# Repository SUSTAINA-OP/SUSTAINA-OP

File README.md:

<h1 align="center">
  SUSTAINA-OP&trade;
</h1>
  <p align="center">
    Open Hardware Platform Humanoid Robot
  </P>
  <p align="center">
    <image src="https://github.com/SUSTAINA-OP/.github/assets/53966390/7b5091e7-2190-424d-ae3a-13d850ef4622" width="640px" align="center"><br>
    SUSTAINA-OP&trade; RoboCup2022 Edition 
  </P>
      
## What is SUSTAINA-OP&trade; ?
SUSTAINA-OP&trade; is an open hardware platform developed to reduce the high cost of developing robot hardware. It is designed by Masato Kubotera, based on the "[Gankenkun](https://github.com/citbrains/OpenPlatform)" robot series developed by Hiroaki Shimoyoshi. SUSTAINA-OP&trade; was adopted as the official robot of the team "[CIT Brains](https://github.com/citbrains)" of Chiba Institute of Technology in Japan, and won the world championship of RoboCup Humanoid League KidSize in 2022.

> [!CAUTION]
> Copyright for SUSTAINA-OP&trade; is held by Masato Kubotera, not by CIT Brains. The copyright has not been completely abandoned.

## Development Environments
The mechanism for this product was designed in **Autodesk Inventor 2022**.

## License Information
This product is open source. Please review the [LICENSE](/LICENSE) for license information.<br>

This product by Masato Kubotera is licensed under a [CC BY-NC-SA 4.0 DEED](http://creativecommons.org/licenses/by-nc-sa/4.0/).

> [!NOTE]
> **Summary:**
> - **Attribution** — You must give appropriate credit , provide a link to the license, and indicate if changes were made.
> - **NonCommercial** — You may not use the material for commercial purposes.
> - **ShareAlike** — If you remix, transform, or build upon the material, you must distribute your contributions under the same license as the original.

> [!TIP]
> - **Examples of appropriate credit** — [SUSTAINA-OP&trade;](https://github.com/SUSTAINA-OP/SUSTAINA-OP) &copy; Masato Kubotera (2022) CC BY-NC-SA 4.0 DEED
> >
> - **Reference & Citation**  
>   To reference and/or cite the work contained in this repository, please use the following publications:
>   - Kubotera, M. and Hayashibara, Y.: SUSTAINA-OP&trade;: Kid-sized Open Hardware Platform Humanoid Robot with Emphasis on Sustainability. RoboCup 2023: Robot World Cup XXVI, pp.166–178 (2024) [Springer](https://link.springer.com/chapter/10.1007/978-3-031-55015-7_14)

> [!IMPORTANT]
> - **Handling of work products** — All work products related to SUSTAINA-OP&trade; should be released as open source, even if they are utilized in a narrow community where closed development may be a priority.
> - **Request for prior inquiry** —  The developer of SUSTAINA-OP&trade; is currently employed at the Chiba Institute of Technology. If you are a student at or related to the University and wish to use the SUSTAINA-OP&trade; deliverables, please contact us in advance.

## Acknowledgements
SUSTAINA-OP&trade; is a robot that incorporates the expertise accumulated by former CIT Brains members who participated in the RoboCup Humanoid League. CIT Brains members collaborated with us in building the actual robots. Additionally, I drew inspiration from various open-source hardware while designing and developing the robot. I would like to express my gratitude to these individuals.

## Contact
If you have any questions, please contact the designer of this product, Masato Kubodera, by [E-mail](masatokubotera06@yahoo.co.jp).

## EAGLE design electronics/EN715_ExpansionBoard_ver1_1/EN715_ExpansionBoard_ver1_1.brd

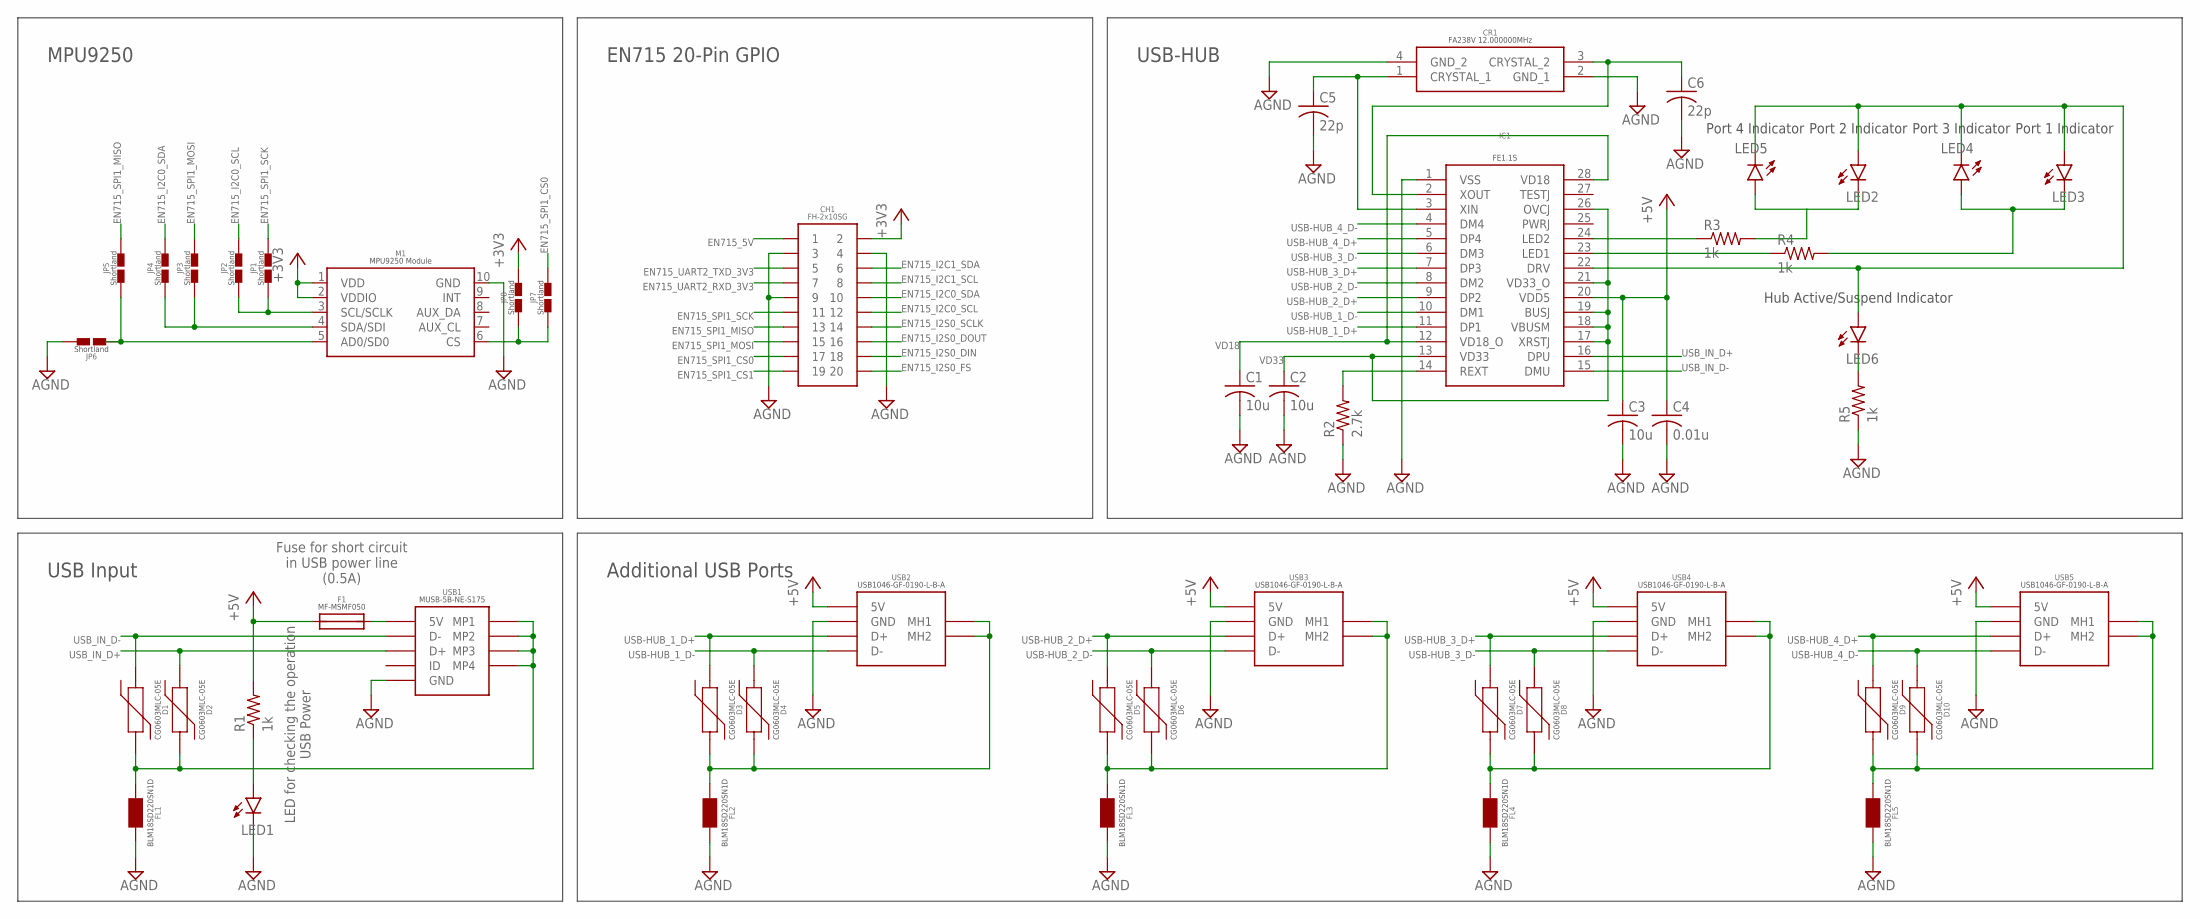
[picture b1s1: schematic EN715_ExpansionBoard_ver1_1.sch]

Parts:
C1, C2, C3: 10u; C0603
C4: 0.01u; C0603
C5, C6: 22p; C0603
CH1: 2X10
CR1: FA238V_12.000000MHZ; FA238V
D1, D2, D3, D4, D5, D6, D7, D8, D9, D10: CG0603MLC-05E
F1: MF-MSMF050
FL1, FL2, FL3, FL4, FL5: BLM18SD220SN1D
IC1: FE1.1S
JP1, JP2, JP3, JP4, JP5, JP6, JP7, JP8: SHORTLAND
LED1, LED2, LED3, LED4, LED5, LED6: LEDSML0603; SML0603
M1: MPU9250_MODULE
R1, R3, R4, R5: 1k; R0603
R2: 2.7k; R0603
USB1: MINI_USB_B_SMD
USB2, USB3, USB4, USB5: USB_A_X1_SMD

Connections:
+3V3: CH1.2, JP8.2, M1.1 (VDD), M1.2 (VDDIO)
+5V: C3.1, C4.1, F1.1, IC1.20 (VDD5), R1.2, USB2.1 (5V), USB3.1 (5V), USB4.1 (5V), USB5.1 (5V)
AGND: C1.2, C2.2, C3.2, C4.2, C5.2, C6.2, CH1.3, CH1.4, CH1.9, CR1.2 (GND_1), CR1.4 (GND_2), FL1.2, FL2.2, FL3.2, FL4.2, FL5.2, IC1.1 (VSS), JP6.2, LED1.C, M1.10 (GND), R2.1, R5.1, USB1.5 (GND), USB2.4 (GND), USB3.4 (GND), USB4.4 (GND), USB5.4 (GND)
B_FUSE_USB_MINI_B: F1.2, USB1.1 (5V)
EN715_5V: CH1.1
EN715_I2C0_SCL: CH1.12, JP2.2
EN715_I2C0_SDA: CH1.10, JP4.2
EN715_I2C1_SCL: CH1.8
EN715_I2C1_SDA: CH1.6
EN715_I2S0_DIN: CH1.18
EN715_I2S0_DOUT: CH1.16
EN715_I2S0_FS: CH1.20
EN715_I2S0_SCLK: CH1.14
EN715_SPI1_CS0: CH1.17, JP7.2
EN715_SPI1_CS1: CH1.19
EN715_SPI1_MISO: CH1.13, JP5.2
EN715_SPI1_MOSI: CH1.15, JP3.2
EN715_SPI1_SCK: CH1.11, JP1.2
EN715_UART2_RXD_3V3: CH1.7
EN715_UART2_TXD_3V3: CH1.5
FE1.1S_DRV: IC1.22 (DRV), LED2.A, LED3.A, LED4.C, LED5.C, LED6.A
FE1.1S_DRV_LED_A: LED6.C, R5.2
FE1.1S_LED1_A: LED3.C, LED4.A, R4.2
FE1.1S_LED_1_B: IC1.23 (LED1), R4.1
FE1.1S_LED_2_A: LED2.C, LED5.A, R3.2
FE1.1S_LED_2_B: IC1.24 (LED2), R3.1
LED_USBIN: LED1.A, R1.1
MPU9250_AD0/SD0: JP5.1, JP6.1, M1.5 (AD0/SD0)
MPU9250_CS: JP7.1, JP8.1, M1.6 (CS)
MPU9250_SCL/SCLK: JP1.1, JP2.1, M1.3 (SCL/SCLK)
MPU9250_SDA/SDI: JP3.1, JP4.1, M1.4 (SDA/SDI)
REXT_FE1.1S: IC1.14 (REXT), R2.2
USB-HUB_1_D+: D3.1, IC1.11 (DP1), USB2.3 (D+)
USB-HUB_1_D-: D4.1, IC1.10 (DM1), USB2.2 (D-)
USB-HUB_2_D+: D5.1, IC1.9 (DP2), USB3.3 (D+)
USB-HUB_2_D-: D6.1, IC1.8 (DM2), USB3.2 (D-)
USB-HUB_3_D+: D7.1, IC1.7 (DP3), USB4.3 (D+)
USB-HUB_3_D-: D8.1, IC1.6 (DM3), USB4.2 (D-)
USB-HUB_4_D+: D9.1, IC1.5 (DP4), USB5.3 (D+)
USB-HUB_4_D-: D10.1, IC1.4 (DM4), USB5.2 (D-)
USB_A_1_SHIELD: D3.2, D4.2, FL2.1, USB2.MH1, USB2.MH2
USB_A_2_SHIELD: D5.2, D6.2, FL3.1, USB3.MH1, USB3.MH2
USB_A_3_SHIELD: D7.2, D8.2, FL4.1, USB4.MH1, USB4.MH2
USB_A_4_SHIELD: D9.2, D10.2, FL5.1, USB5.MH1, USB5.MH2
USB_IN_D+: D2.1, IC1.16 (DPU), USB1.3 (D+)
USB_IN_D-: D1.1, IC1.15 (DMU), USB1.2 (D-)
USB_MINI_B_SHIELD: D1.2, D2.2, FL1.1, USB1.MP1, USB1.MP2, USB1.MP3, USB1.MP4
VD18: C1.1, IC1.12 (VD18_O), IC1.28 (VD18)
VD33: C2.1, IC1.13 (VD33), IC1.17 (XRSTJ), IC1.18 (VBUSM), IC1.19 (BUSJ), IC1.21 (VD33_O), IC1.26 (OVCJ)
XIN_FE1.1S: C5.1, CR1.1 (CRYSTAL_1), IC1.3 (XIN)
XOUT_FE1.1S: C6.1, CR1.3 (CRYSTAL_2), IC1.2 (XOUT)

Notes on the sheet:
Hub Active/Suspend Indicator
Port 1 Indicator
Port 2 Indicator
USB-HUB
Additional USB Ports
USB Input
Fuse for short circuit in USB power line (0.5A)
LED for checking the operation USB Power
EN715 20-Pin GPIO
MPU9250
Port 3 Indicator
Port 4 Indicator

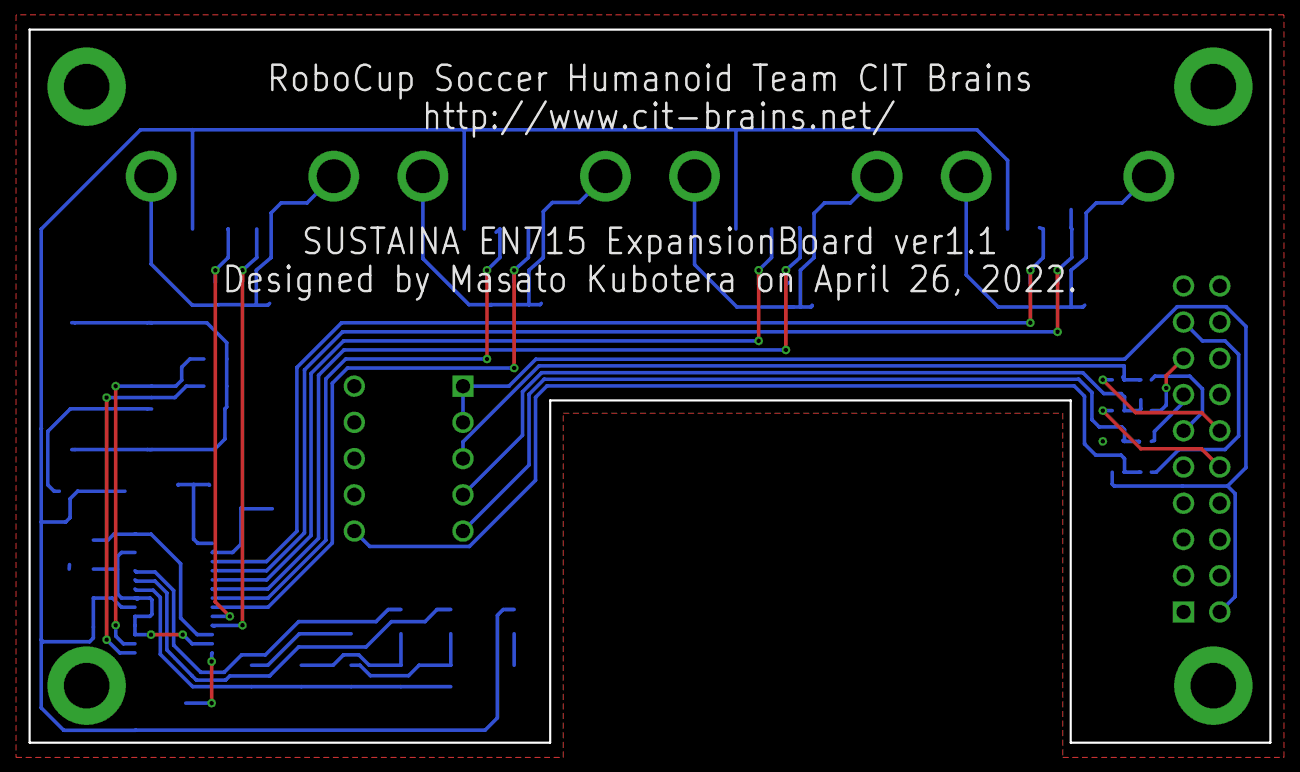
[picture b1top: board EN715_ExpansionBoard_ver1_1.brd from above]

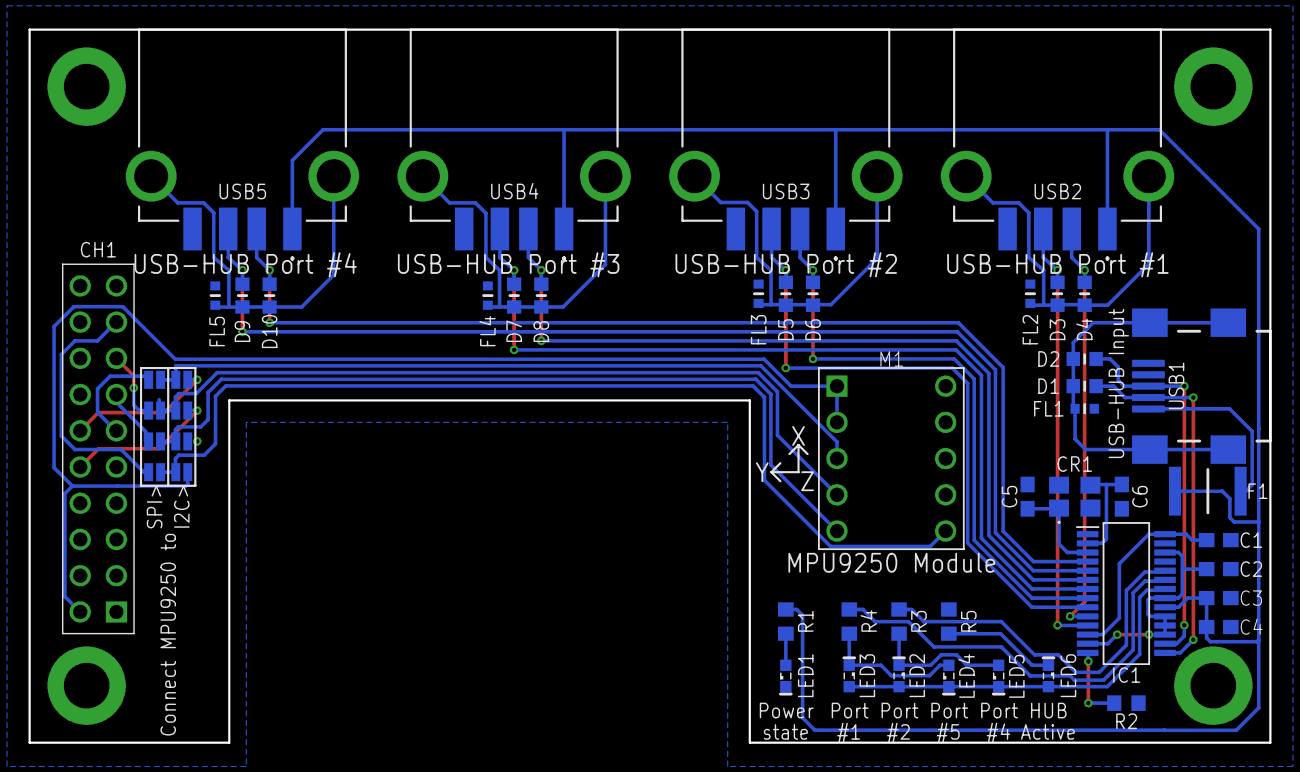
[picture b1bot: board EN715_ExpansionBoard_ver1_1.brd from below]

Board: 2 copper layers, 87.0 x 50.0 mm, 50 parts (50 on the bottom side), 41 nets.

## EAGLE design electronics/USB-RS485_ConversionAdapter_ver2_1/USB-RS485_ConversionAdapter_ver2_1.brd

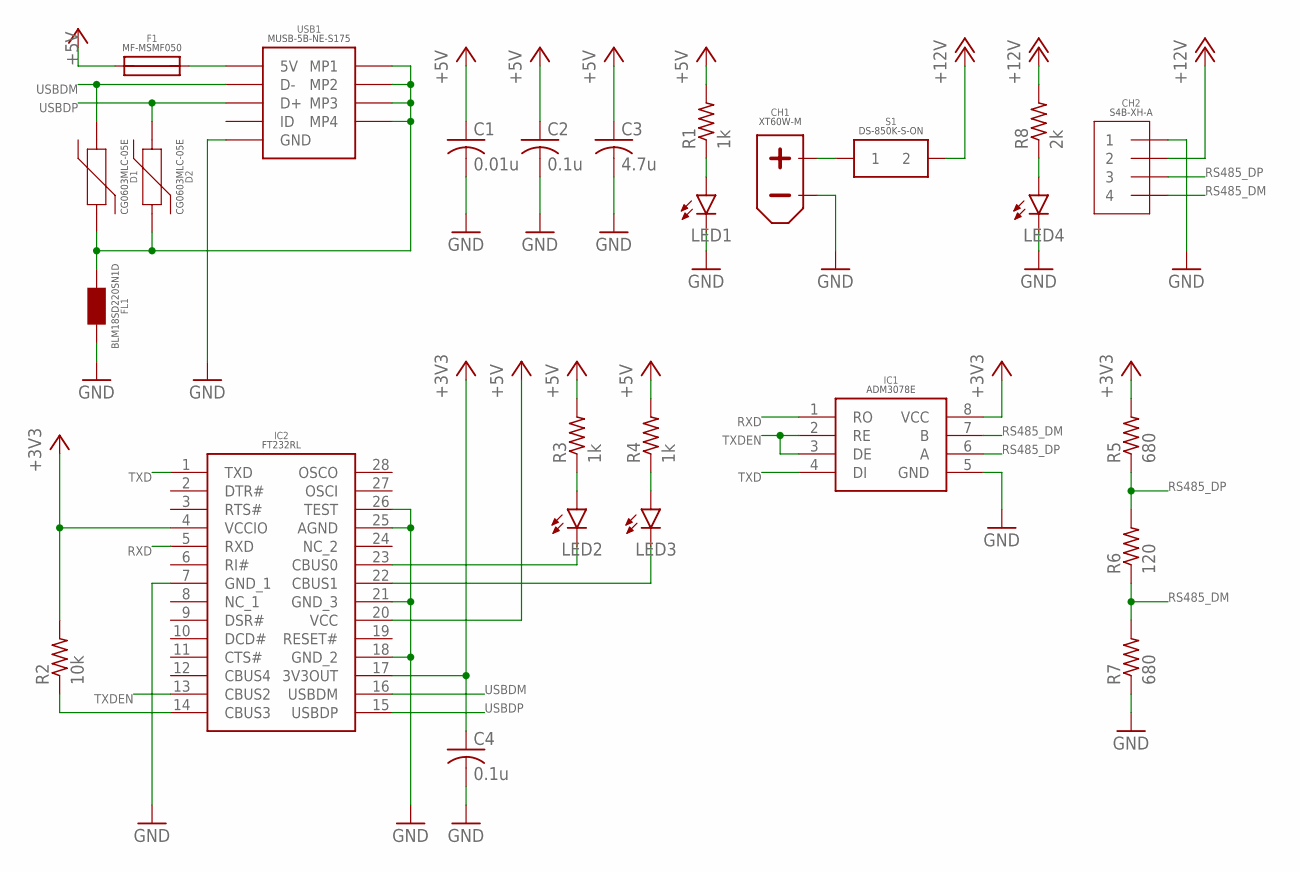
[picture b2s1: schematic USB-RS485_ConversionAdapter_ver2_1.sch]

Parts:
C1: 0.01u; C0603
C2, C4: 0.1u; C0603
C3: 4.7u; C0603
CH1: XT60PW-M
CH2: S4B-XH-A
D1, D2: CG0603MLC-05E
F1: MF-MSMF050
FL1: BLM18SD220SN1D
IC1: ADM3078E
IC2: FT232RL
LED1, LED2, LED3, LED4: LEDSML0603; SML0603
R1, R3, R4: 1k; R0603
R2: 10k; R0603
R5, R7: 680; R0603
R6: 120; R0603
R8: 2k; R0603
S1: DS-850K-S-ON
USB1: MINI_USB_B_SMD

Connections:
5V_LED: LED1.A, R1.1
12V_LED: LED4.A, R8.1
+3V3: C4.1, IC1.8 (VCC), IC2.4 (VCCIO), IC2.17 (3V3OUT), R2.2, R5.2
+5V: C1.1, C2.1, C3.1, F1.1, IC2.20 (VCC), R1.2, R3.2, R4.2
+12V: CH2.2, R8.2, S1.2B (2), S1.2T (2)
BEFORE_+12V: CH1.+, S1.1B (1), S1.1T (1)
B_FUSE_USB_MINI_B: F1.2, USB1.1 (5V)
CBUS0: IC2.23 (CBUS0), LED2.C
CBUS1: IC2.22 (CBUS1), LED3.C
CBUS3: IC2.14 (CBUS3), R2.1
GND: C1.2, C2.2, C3.2, C4.2, CH1.-, CH2.1, FL1.2, IC1.5 (GND), IC2.7 (GND_1), IC2.18 (GND_2), IC2.21 (GND_3), IC2.25 (AGND), IC2.26 (TEST), LED1.C, LED4.C, R7.1, USB1.5 (GND)
RS485_DM: CH2.4, IC1.7 (B), R6.1, R7.2
RS485_DP: CH2.3, IC1.6 (A), R5.1, R6.2
RXD: IC1.1 (RO), IC2.5 (RXD)
RXLED#: LED3.A, R4.1
TXD: IC1.4 (DI), IC2.1 (TXD)
TXDEN: IC1.2 (RE), IC1.3 (DE), IC2.13 (CBUS2)
TXLED#: LED2.A, R3.1
USBDM: D1.1, IC2.16 (USBDM), USB1.2 (D-)
USBDP: D2.1, IC2.15 (USBDP), USB1.3 (D+)
USB_MINI_B_SHIELD: D1.2, D2.2, FL1.1, USB1.MP1, USB1.MP2, USB1.MP3, USB1.MP4

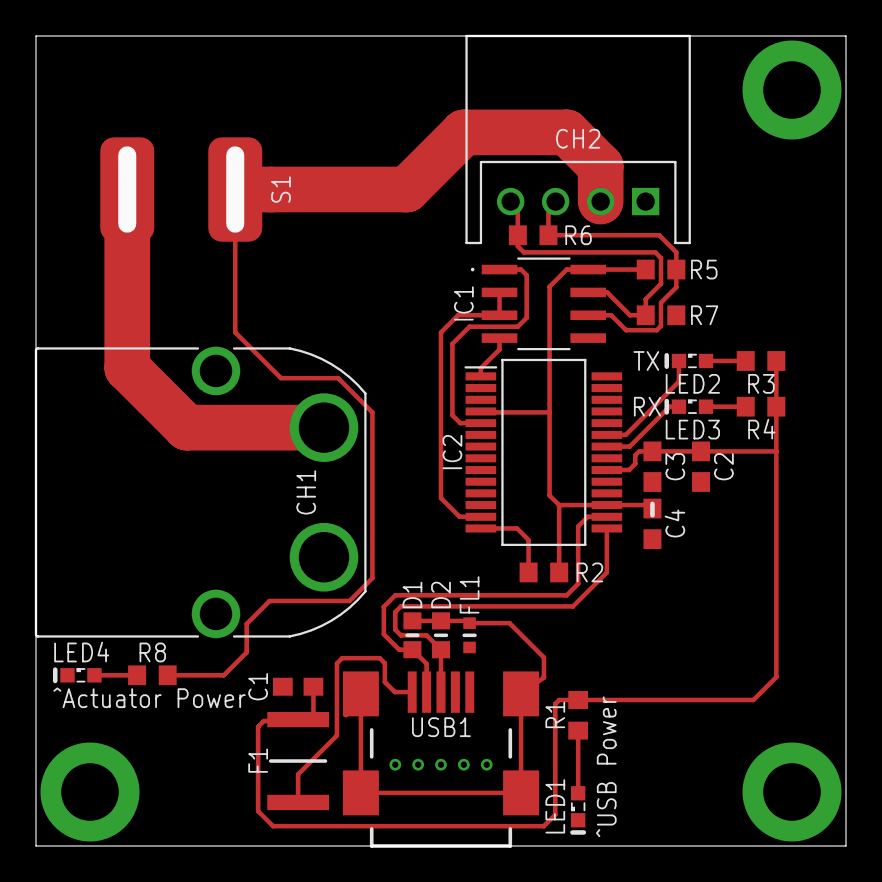
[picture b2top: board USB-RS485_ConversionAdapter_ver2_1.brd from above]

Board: 2 copper layers, 44.0 x 44.0 mm, 26 parts (0 on the bottom side), 21 nets.

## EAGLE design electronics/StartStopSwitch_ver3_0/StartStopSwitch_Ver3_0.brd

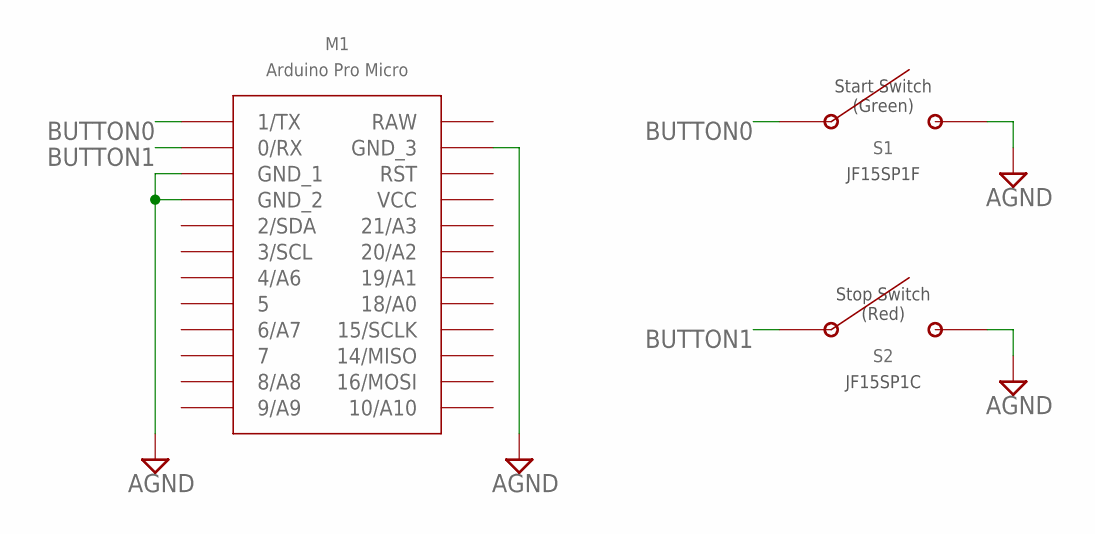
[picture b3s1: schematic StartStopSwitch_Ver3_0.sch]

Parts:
M1: PRO_MICRO_SMD
S1: JF15SP1F; JF15SP1
S2: JF15SP1C; JF15SP1

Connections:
AGND: M1.3 (GND_1), M1.4 (GND_2), M1.23 (GND_3), S1.3, S1.4, S2.3, S2.4
BUTTON0: M1.1 (1/TX), S1.1, S1.2
BUTTON1: M1.2 (0/RX), S2.1, S2.2

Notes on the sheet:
Start Switch (Green)
Stop Switch (Red)

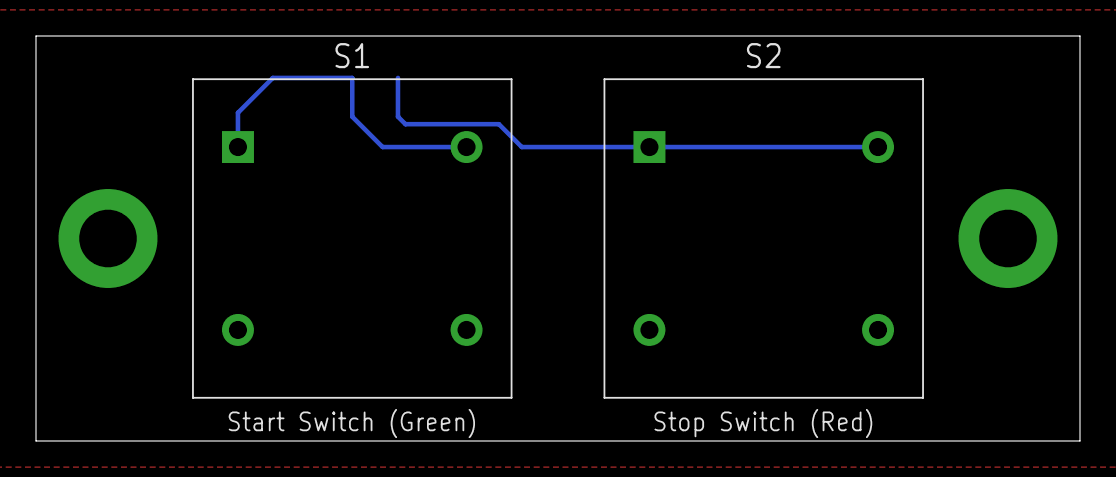
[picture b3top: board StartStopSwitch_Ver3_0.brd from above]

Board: 2 copper layers, 58.0 x 22.5 mm, 3 parts (1 on the bottom side), 3 nets.

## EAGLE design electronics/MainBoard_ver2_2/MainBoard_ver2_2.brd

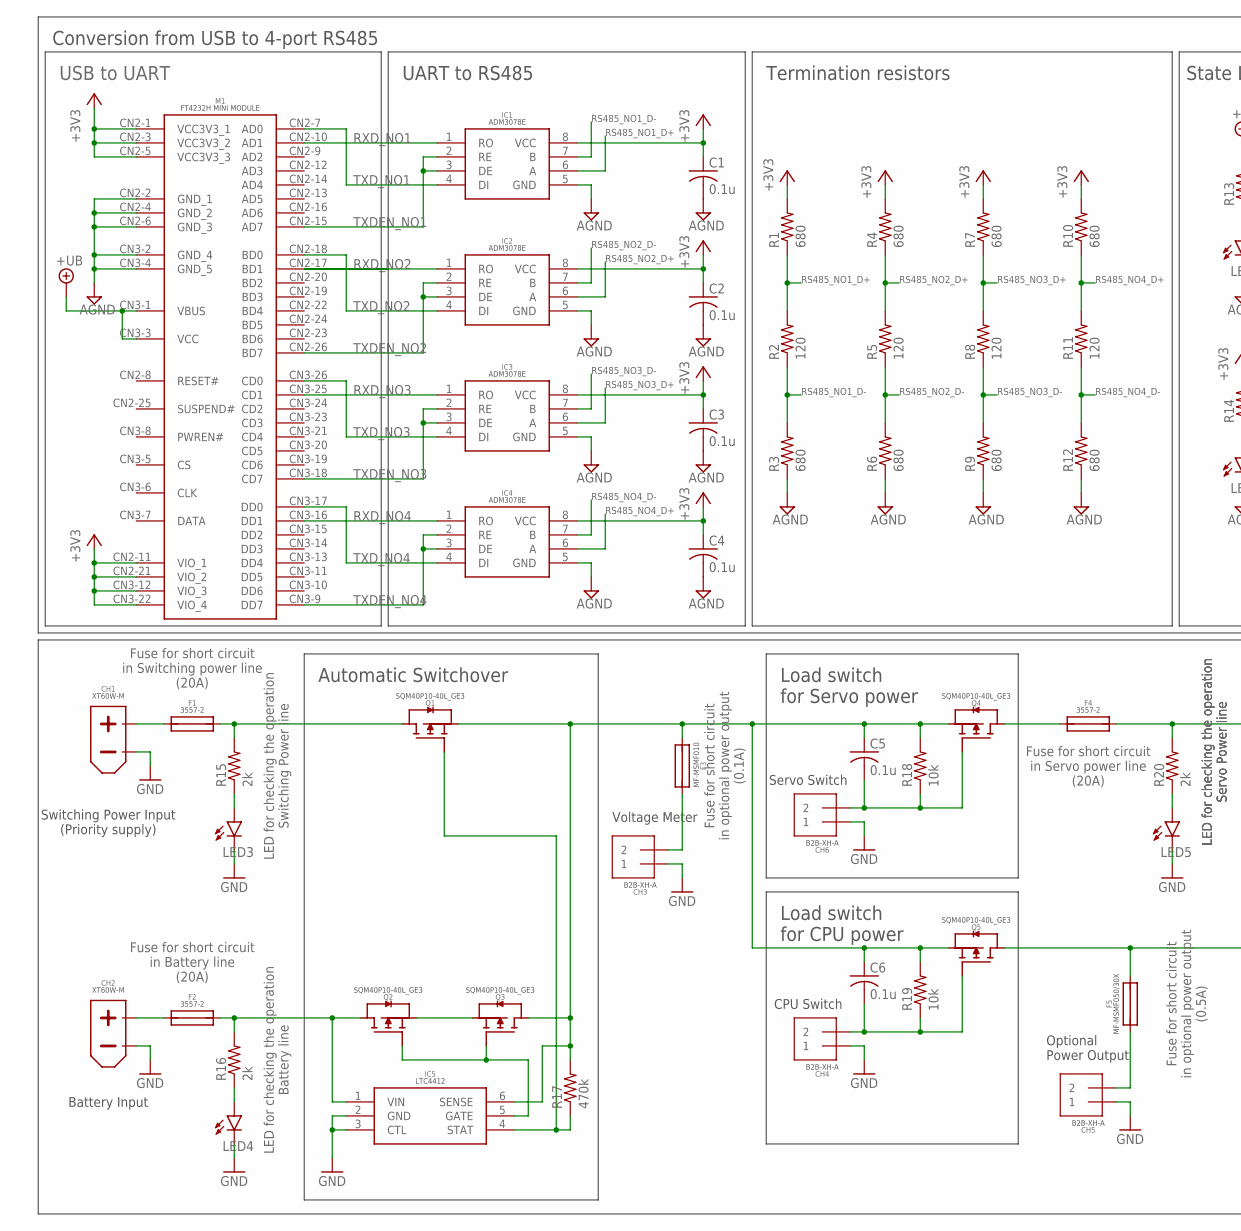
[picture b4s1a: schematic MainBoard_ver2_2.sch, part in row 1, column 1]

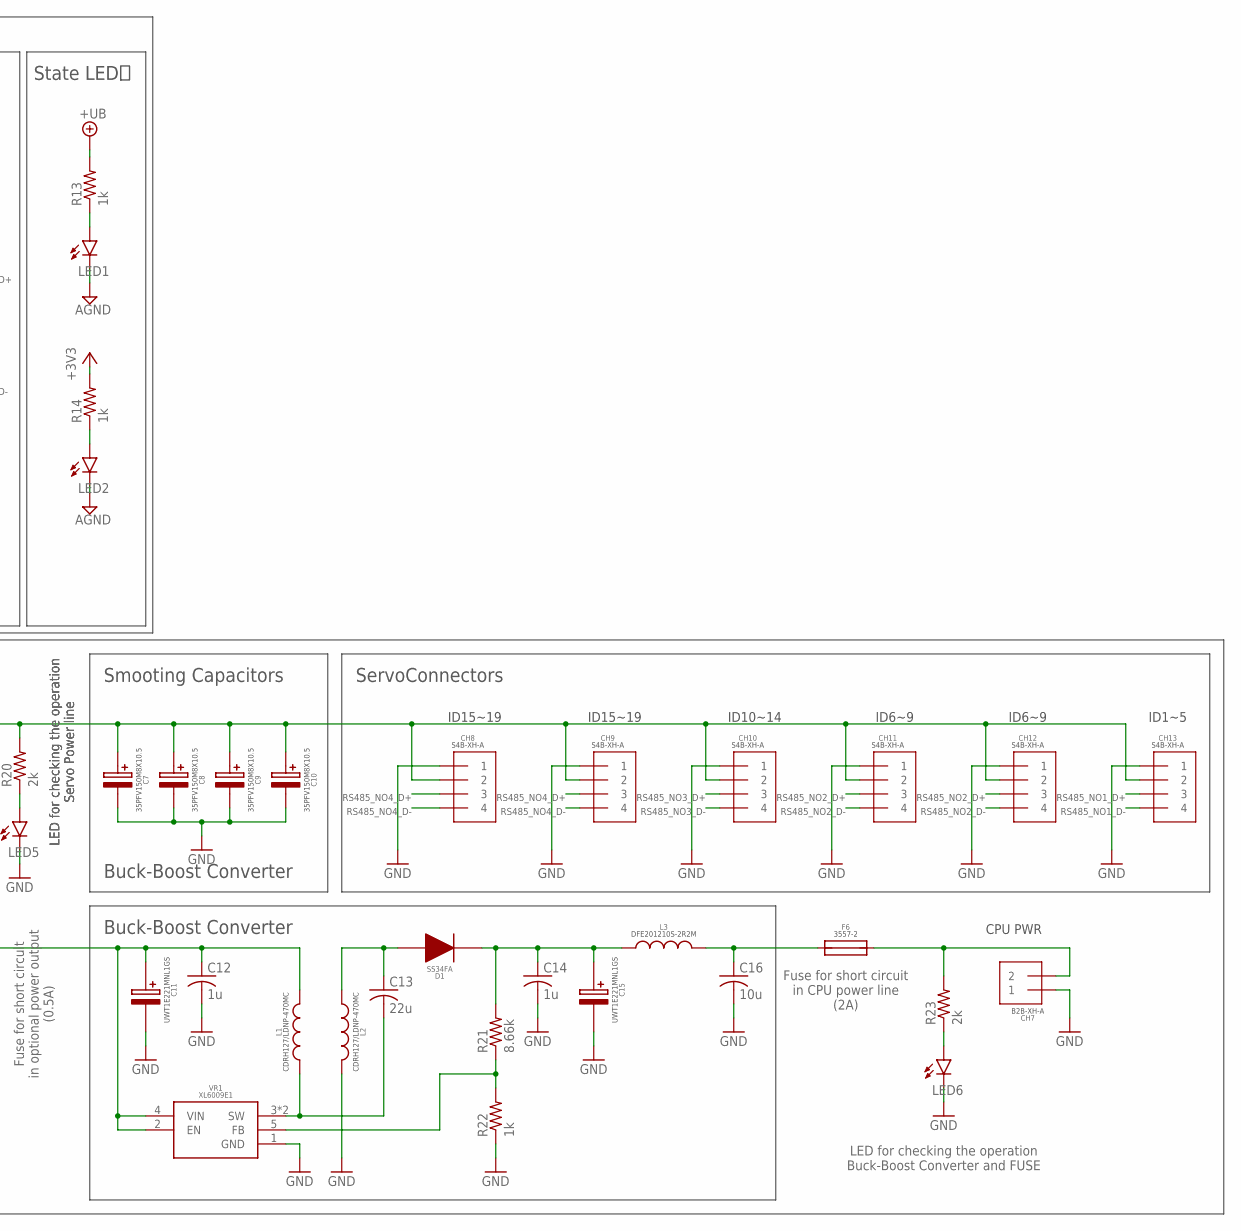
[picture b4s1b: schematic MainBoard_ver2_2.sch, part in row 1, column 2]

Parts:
C1, C2, C3, C4, C5, C6: 0.1u; C0603
C7, C8, C9, C10: 35PFV150M8X10.5
C11, C15: UWT1E221MNL1GS
C12, C14: 1u; C0603
C13: 22u; C2012
C16: 10u; C0603
CH1, CH2: XT60PW-M
CH3, CH4, CH5, CH6, CH7: B2B-XH-A
CH8, CH9, CH10, CH11, CH12, CH13: S4B-XH-A
D1: SS34FA
F1, F2, F4, F6: 3557-2
F3: MF-MSMF010
F5: MF-MSMF050/30X; MF-MSMF050
IC1, IC2, IC3, IC4: ADM3078E
IC5: LTC4412
L1, L2: CDRH127/LDNP-470MC; CDRH127/LDNP
L3: DFE201210S-2R2M; DFE201210S
LED1, LED2, LED3, LED4, LED5, LED6: LEDSML0603; SML0603
M1: FT4232H_MINI_MODULE
Q1, Q2, Q3, Q4, Q5: SQM40P10-40L_GE3; TO-252-3
R1, R3, R4, R6, R7, R9, R10, R12: 680; R0603
R2, R5, R8, R11: 120; R0603
R13, R14, R22: 1k; R0603
R15, R16, R20, R23: 2k; R0603
R17: 470k; R0603
R18, R19: 10k; R0603
R21: 8.66k; R0603
VR1: XL6009E1; TO263-5L

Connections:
+3V3: C1.1, C2.1, C3.1, C4.1, IC1.8 (VCC), IC2.8 (VCC), IC3.8 (VCC), IC4.8 (VCC), M1.CN2-1 (VCC3V3_1), M1.CN2-3 (VCC3V3_2), M1.CN2-5 (VCC3V3_3), M1.CN2-11 (VIO_1), M1.CN2-21 (VIO_2), M1.CN3-12 (VIO_3), M1.CN3-22 (VIO_4), R1.2, R4.2, R7.2, R10.2, R14.2
+UB: M1.CN3-1 (VBUS), M1.CN3-3 (VCC), R13.2
AGND: C1.2, C2.2, C3.2, C4.2, IC1.5 (GND), IC2.5 (GND), IC3.5 (GND), IC4.5 (GND), LED1.C, LED2.C, M1.CN2-2 (GND_1), M1.CN2-4 (GND_2), M1.CN2-6 (GND_3), M1.CN3-2 (GND_4), M1.CN3-4 (GND_5), R3.1, R6.1, R9.1, R12.1
A_DIODE_DCDC: C14.1, C15.+, D1.1, L3.1, R21.2
A_FUSE_BATT: F2.3 (2), F2.4 (2), IC5.1 (VIN), Q2.4 (D), R16.2
A_FUSE_DCDC: CH7.2, F6.3 (2), F6.4 (2), R23.2
A_FUSE_METER: CH3.2, F3.2
A_FUSE_PWR: F1.3 (2), F1.4 (2), Q1.4 (D), R15.2
A_FUSE_SERVO: C7.+, C8.+, C9.+, C10.+, CH8.2, CH9.2, CH10.2, CH11.2, CH12.2, CH13.2, F4.3 (2), F4.4 (2), R20.2
B_DIODE_DCDC: C13.1, D1.2, L2.1
B_FUSE_BATT: CH2.+, F2.1, F2.2 (1)
B_FUSE_DCDC: C16.1, F6.1, F6.2 (1), L3.2
B_FUSE_PWR: CH1.+, F1.1, F1.2 (1)
B_FUSE_SERVO: F4.1, F4.2 (1), Q4.4 (D)
B_LOAD_CPU: C6.2, CH4.2, Q5.1 (G), R19.1
B_LOAD_SERVO: C5.2, CH6.2, Q4.1 (G), R18.1
CPU_PWR_IN: C11.+, C12.1, F5.2, L1.2, Q5.4 (D), VR1.2 (EN), VR1.4 (VIN)
FB_DCDC: R21.1, R22.2, VR1.5 (FB)
GND: C7.-, C8.-, C9.-, C10.-, C11.-, C12.2, C14.2, C15.-, C16.2, CH1.-, CH2.-, CH3.1, CH4.1, CH5.1, CH6.1, CH7.1, CH8.1, CH9.1, CH10.1, CH11.1, CH12.1, CH13.1, IC5.2 (GND), IC5.3 (CTL), L2.2, LED3.C, LED4.C, LED5.C, LED6.C, R22.1, VR1.1 (GND)
INPUT_PWR: C5.1, C6.1, F3.1, IC5.6 (SENSE), Q1.3 (S), Q3.4 (D), Q4.3 (S), Q5.3 (S), R17.2, R18.2, R19.2
LED_3V3: LED2.A, R14.1
LED_BATT: LED4.A, R16.1
LED_DCDCOUT: LED6.A, R23.1
LED_PWR: LED3.A, R15.1
LED_SERVO: LED5.A, R20.1
LED_UB: LED1.A, R13.1
LTC4412_GATE: IC5.5 (GATE), Q2.1 (G), Q3.1 (G)
LTC4412_STAT: IC5.4 (STAT), Q1.1 (G), R17.1
POWER_OUTPUT: CH5.2, F5.1
RS485_NO1_D+: CH13.3, IC1.6 (A), R1.1, R2.2
RS485_NO1_D-: CH13.4, IC1.7 (B), R2.1, R3.2
RS485_NO2_D+: CH11.3, CH12.3, IC2.6 (A), R4.1, R5.2
RS485_NO2_D-: CH11.4, CH12.4, IC2.7 (B), R5.1, R6.2
RS485_NO3_D+: CH10.3, IC3.6 (A), R7.1, R8.2
RS485_NO3_D-: CH10.4, IC3.7 (B), R8.1, R9.2
RS485_NO4_D+: CH8.3, CH9.3, IC4.6 (A), R10.1, R11.2
RS485_NO4_D-: CH8.4, CH9.4, IC4.7 (B), R11.1, R12.2
RXD_NO1: IC1.1 (RO), M1.CN2-10 (AD1)
RXD_NO2: IC2.1 (RO), M1.CN2-17 (BD1)
RXD_NO3: IC3.1 (RO), M1.CN3-25 (CD1)
RXD_NO4: IC4.1 (RO), M1.CN3-16 (DD1)
SOURCE: Q2.3 (S), Q3.3 (S)
SW_DCDC: C13.2, L1.1, VR1.3 (SW), VR1.6 (SW)
TXDEN_NO1: IC1.2 (RE), IC1.3 (DE), M1.CN2-15 (AD7)
TXDEN_NO2: IC2.2 (RE), IC2.3 (DE), M1.CN2-26 (BD7)
TXDEN_NO3: IC3.2 (RE), IC3.3 (DE), M1.CN3-18 (CD7)
TXDEN_NO4: IC4.2 (RE), IC4.3 (DE), M1.CN3-9 (DD7)
TXD_NO1: IC1.4 (DI), M1.CN2-7 (AD0)
TXD_NO2: IC2.4 (DI), M1.CN2-18 (BD0)
TXD_NO3: IC3.4 (DI), M1.CN3-26 (CD0)
TXD_NO4: IC4.4 (DI), M1.CN3-17 (DD0)

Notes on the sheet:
CPU Switch
Battery Input
Switching Power Input (Priority supply)
Servo Switch
Voltage Meter
Optional Power Output
ServoConnectors
Buck-Boost Converter
Smooting Capacitors
LED for checking the operation Buck-Boost Converter and FUSE
Fuse for short circuit in CPU power line (2A)
CPU PWR
Fuse for short circuit in Servo power line (20A)
Load switch for Servo power
Load switch for CPU power
Fuse for short circuit in optional power output (0.5A)
Automatic Switchover
Fuse for short circuit in Switching power line (20A)
Fuse for short circuit in Battery line (20A)
LED for checking the operation Switching Power line
LED for checking the operation Battery line
Fuse for short circuit in optional power output (0.1A)
LED for checking the operation Servo Power line
ID1~5
ID6~9
ID10~14
ID15~19
USB to UART
Conversion from USB to 4-port RS485
UART to RS485
Termination resistors
State LEDｓ

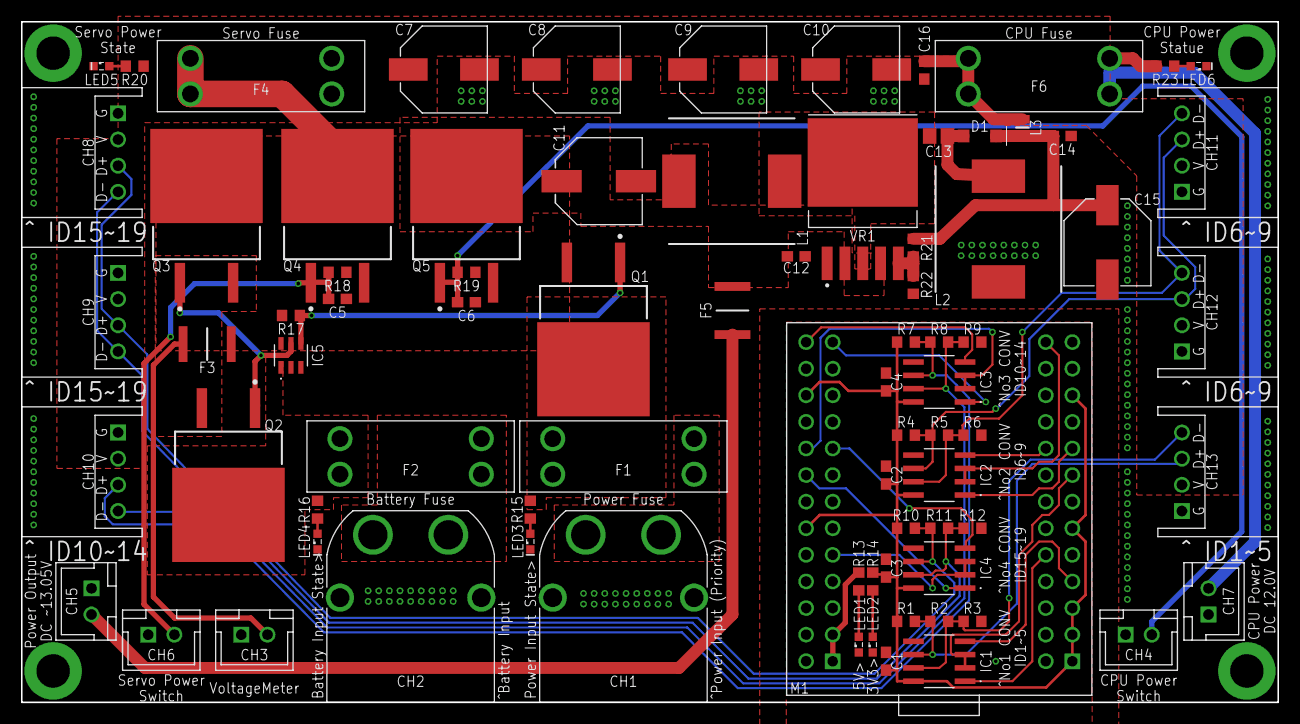
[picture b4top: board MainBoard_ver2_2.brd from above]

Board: 2 copper layers, 120.0 x 65.0 mm, 80 parts (0 on the bottom side), 51 nets.

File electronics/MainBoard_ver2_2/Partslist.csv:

Partlist

Exported from MainBoard_ver2_2.sch at 2022/04/10 19:26

EAGLE Version 9.6.2 Copyright (c) 1988-2020 Autodesk, Inc.

Assembly variant: 

Part     Value               Device              Package             Library             Sheet

C1       0.1u                C-USC0603           C0603               rcl                 1
C2       0.1u                C-USC0603           C0603               rcl                 1
C3       0.1u                C-USC0603           C0603               rcl                 1
C4       0.1u                C-USC0603           C0603               rcl                 1
C5       0.1u                C-USC0603           C0603               rcl                 1
C6       0.1u                C-USC0603           C0603               rcl                 1
C7       35PFV150M8X10.5     35PFV150M8X10.5     35PFV150M8X10.5     35PFV150M8X10.5     1
C8       35PFV150M8X10.5     35PFV150M8X10.5     35PFV150M8X10.5     35PFV150M8X10.5     1
C9       35PFV150M8X10.5     35PFV150M8X10.5     35PFV150M8X10.5     35PFV150M8X10.5     1
C10      35PFV150M8X10.5     35PFV150M8X10.5     35PFV150M8X10.5     35PFV150M8X10.5     1
C11      UWT1E221MNL1GS      UWT1E221MNL1GS      UWT1E221MNL1GS      UWT1E221MNL1GS      1
C12      1u                  C-USC0603           C0603               rcl                 1
C13      22u                 C-USC2012           C2012               rcl                 1
C14      1u                  C-USC0603           C0603               rcl                 1
C15      UWT1E221MNL1GS      UWT1E221MNL1GS      UWT1E221MNL1GS      UWT1E221MNL1GS      1
C16      10u                 C-USC0603           C0603               rcl                 1
CH1      XT60PW-M            XT60PW-M            XT60PW-M            AMASS_XT60          1
CH2      XT60PW-M            XT60PW-M            XT60PW-M            AMASS_XT60          1
CH3      B2B-XH-A            B2B-XH-A            B2B-XH-A            JST-XH              1
CH4      B2B-XH-A            B2B-XH-A            B2B-XH-A            JST-XH              1
CH5      B2B-XH-A            B2B-XH-A            B2B-XH-A            JST-XH              1
CH6      B2B-XH-A            B2B-XH-A            B2B-XH-A            JST-XH              1
CH7      B2B-XH-A            B2B-XH-A            B2B-XH-A            JST-XH              1
CH8      S4B-XH-A            S4B-XH-A            S4B-XH-A            JST-XH              1
CH9      S4B-XH-A            S4B-XH-A            S4B-XH-A            JST-XH              1
CH10     S4B-XH-A            S4B-XH-A            S4B-XH-A            JST-XH              1
CH11     S4B-XH-A            S4B-XH-A            S4B-XH-A            JST-XH              1
CH12     S4B-XH-A            S4B-XH-A            S4B-XH-A            JST-XH              1
CH13     S4B-XH-A            S4B-XH-A            S4B-XH-A            JST-XH              1
D1       SS34FA              SS34FA              SS34FA              SS34FA              1
F1       3557-2              3557-2              3557-2              3557-2              1
F2       3557-2              3557-2              3557-2              3557-2              1
F3       MF-MSMF010          MF-MSMF010          MF-MSMF010          MF-MSMF             1
F4       3557-2              3557-2              3557-2              3557-2              1
F5       MF-MSMF050/30X      MF-MSMF050/30X      MF-MSMF050          MF-MSMF             1
F6       3557-2              3557-2              3557-2              3557-2              1
IC1      ADM3078E            ADM3078E            ADM3078E            ADM3078E            1
IC2      ADM3078E            ADM3078E            ADM3078E            ADM3078E            1
IC3      ADM3078E            ADM3078E            ADM3078E            ADM3078E            1
IC4      ADM3078E            ADM3078E            ADM3078E            ADM3078E            1
IC5      LTC4412             LTC4412             LTC4412             LTC4412             1
L1       CDRH127/LDNP-470MC  CDRH127/LDNP-470MC  CDRH127/LDNP        CDRH127_LDNP        1
L2       CDRH127/LDNP-470MC  CDRH127/LDNP-470MC  CDRH127/LDNP        CDRH127_LDNP        1
L3       DFE201210S-2R2M     DFE201210S-2R2M     DFE201210S          DFE201210S          1
LED1                         LEDSML0603          SML0603             led                 1
LED2                         LEDSML0603          SML0603             led                 1
LED3                         LEDSML0603          SML0603             led                 1
LED4                         LEDSML0603          SML0603             led                 1
M1       FT4232H_MINI_MODULE FT4232H_MINI_MODULE FT4232H_MINI_MODULE FT4232H_MINI_MODULE 1
Q1       SQM40P10-40L_GE3    SQM40P10-40L_GE3    TO-252-3            Vishay_FET          1
Q2       SQM40P10-40L_GE3    SQM40P10-40L_GE3    TO-252-3            Vishay_FET          1
Q3       SQM40P10-40L_GE3    SQM40P10-40L_GE3    TO-252-3            Vishay_FET          1
Q4       SQM40P10-40L_GE3    SQM40P10-40L_GE3    TO-252-3            Vishay_FET          1
Q5       SQM40P10-40L_GE3    SQM40P10-40L_GE3    TO-252-3            Vishay_FET          1
R1       680                 R-US_R0603          R0603               rcl                 1
R2       120                 R-US_R0603          R0603               rcl                 1
R3       680                 R-US_R0603          R0603               rcl                 1
R4       680                 R-US_R0603          R0603               rcl                 1
R5       120                 R-US_R0603          R0603               rcl                 1
R6       680                 R-US_R0603          R0603               rcl                 1
R7       680                 R-US_R0603          R0603               rcl                 1
R8       120                 R-US_R0603          R0603               rcl                 1
R9       680                 R-US_R0603          R0603               rcl                 1
R10      680                 R-US_R0603          R0603               rcl                 1
R11      120                 R-US_R0603          R0603               rcl                 1
R12      680                 R-US_R0603          R0603               rcl                 1
R13      2k                  R-US_R0603          R0603               rcl                 1
R14      2k                  R-US_R0603          R0603               rcl                 1
R15      470k                R-US_R0603          R0603               rcl                 1
R16      10k                 R-US_R0603          R0603               rcl                 1
R17      10k                 R-US_R0603          R0603               rcl                 1
R18      2k                  R-US_R0603          R0603               rcl                 1
R19      8.66k               R-US_R0603          R0603               rcl                 1
R20      1k                  R-US_R0603          R0603               rcl                 1
R21      2k                  R-US_R0603          R0603               rcl                 1
VR1      XL6009E1            XL6009E1            TO263-5L            XL6009E1            1

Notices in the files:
parts and their libraries:
SparkFun-PowerSymbols: Licensing: Creative Commons ShareAlike 4.0 International - https://creativecommons.org/licenses/by-sa/4.0
